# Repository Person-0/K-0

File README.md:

# **K-0**

75% Keyboard with thocky switches. USB-C / BLE connectivity, fully custom 3d printed case + PCB.

## The Idea

Always wanted to design a keyboard for myself. Decided to finally go for it.

After searching online about various keyboards and switches, I realized I love deep thocky-sounding keyboards, so I selected the `Akko Bittersweet` switches. They are tactile switches with an operating force of 48 ± 5gf and tactile force of 60 ± 5gf. ([more switch specs](https://en.akkogear.com/product/bittersweet-switch-lubed/), [sound test](https://www.youtube.com/watch?v=nj9W8xXELII)).

The layout of the keyboard will be 60%, with no separate arrow keys or navigation cluster BUT with an added function keys row.

The microcontroller I have selected for this project is the `MDBT50Q-P1M nRF52840 Based BLE Module` for it's built-in bluetooth capabilities and good support ecosystem for similar projects. This will be paired up with a 1s (3.7V) LiPo battery with a suitable capacity + custom charging circuit which will be good enough for our usecase.

### Keyboard layout (from [keyboard-layout-editor.com](https://keyboard-layout-editor.com)):

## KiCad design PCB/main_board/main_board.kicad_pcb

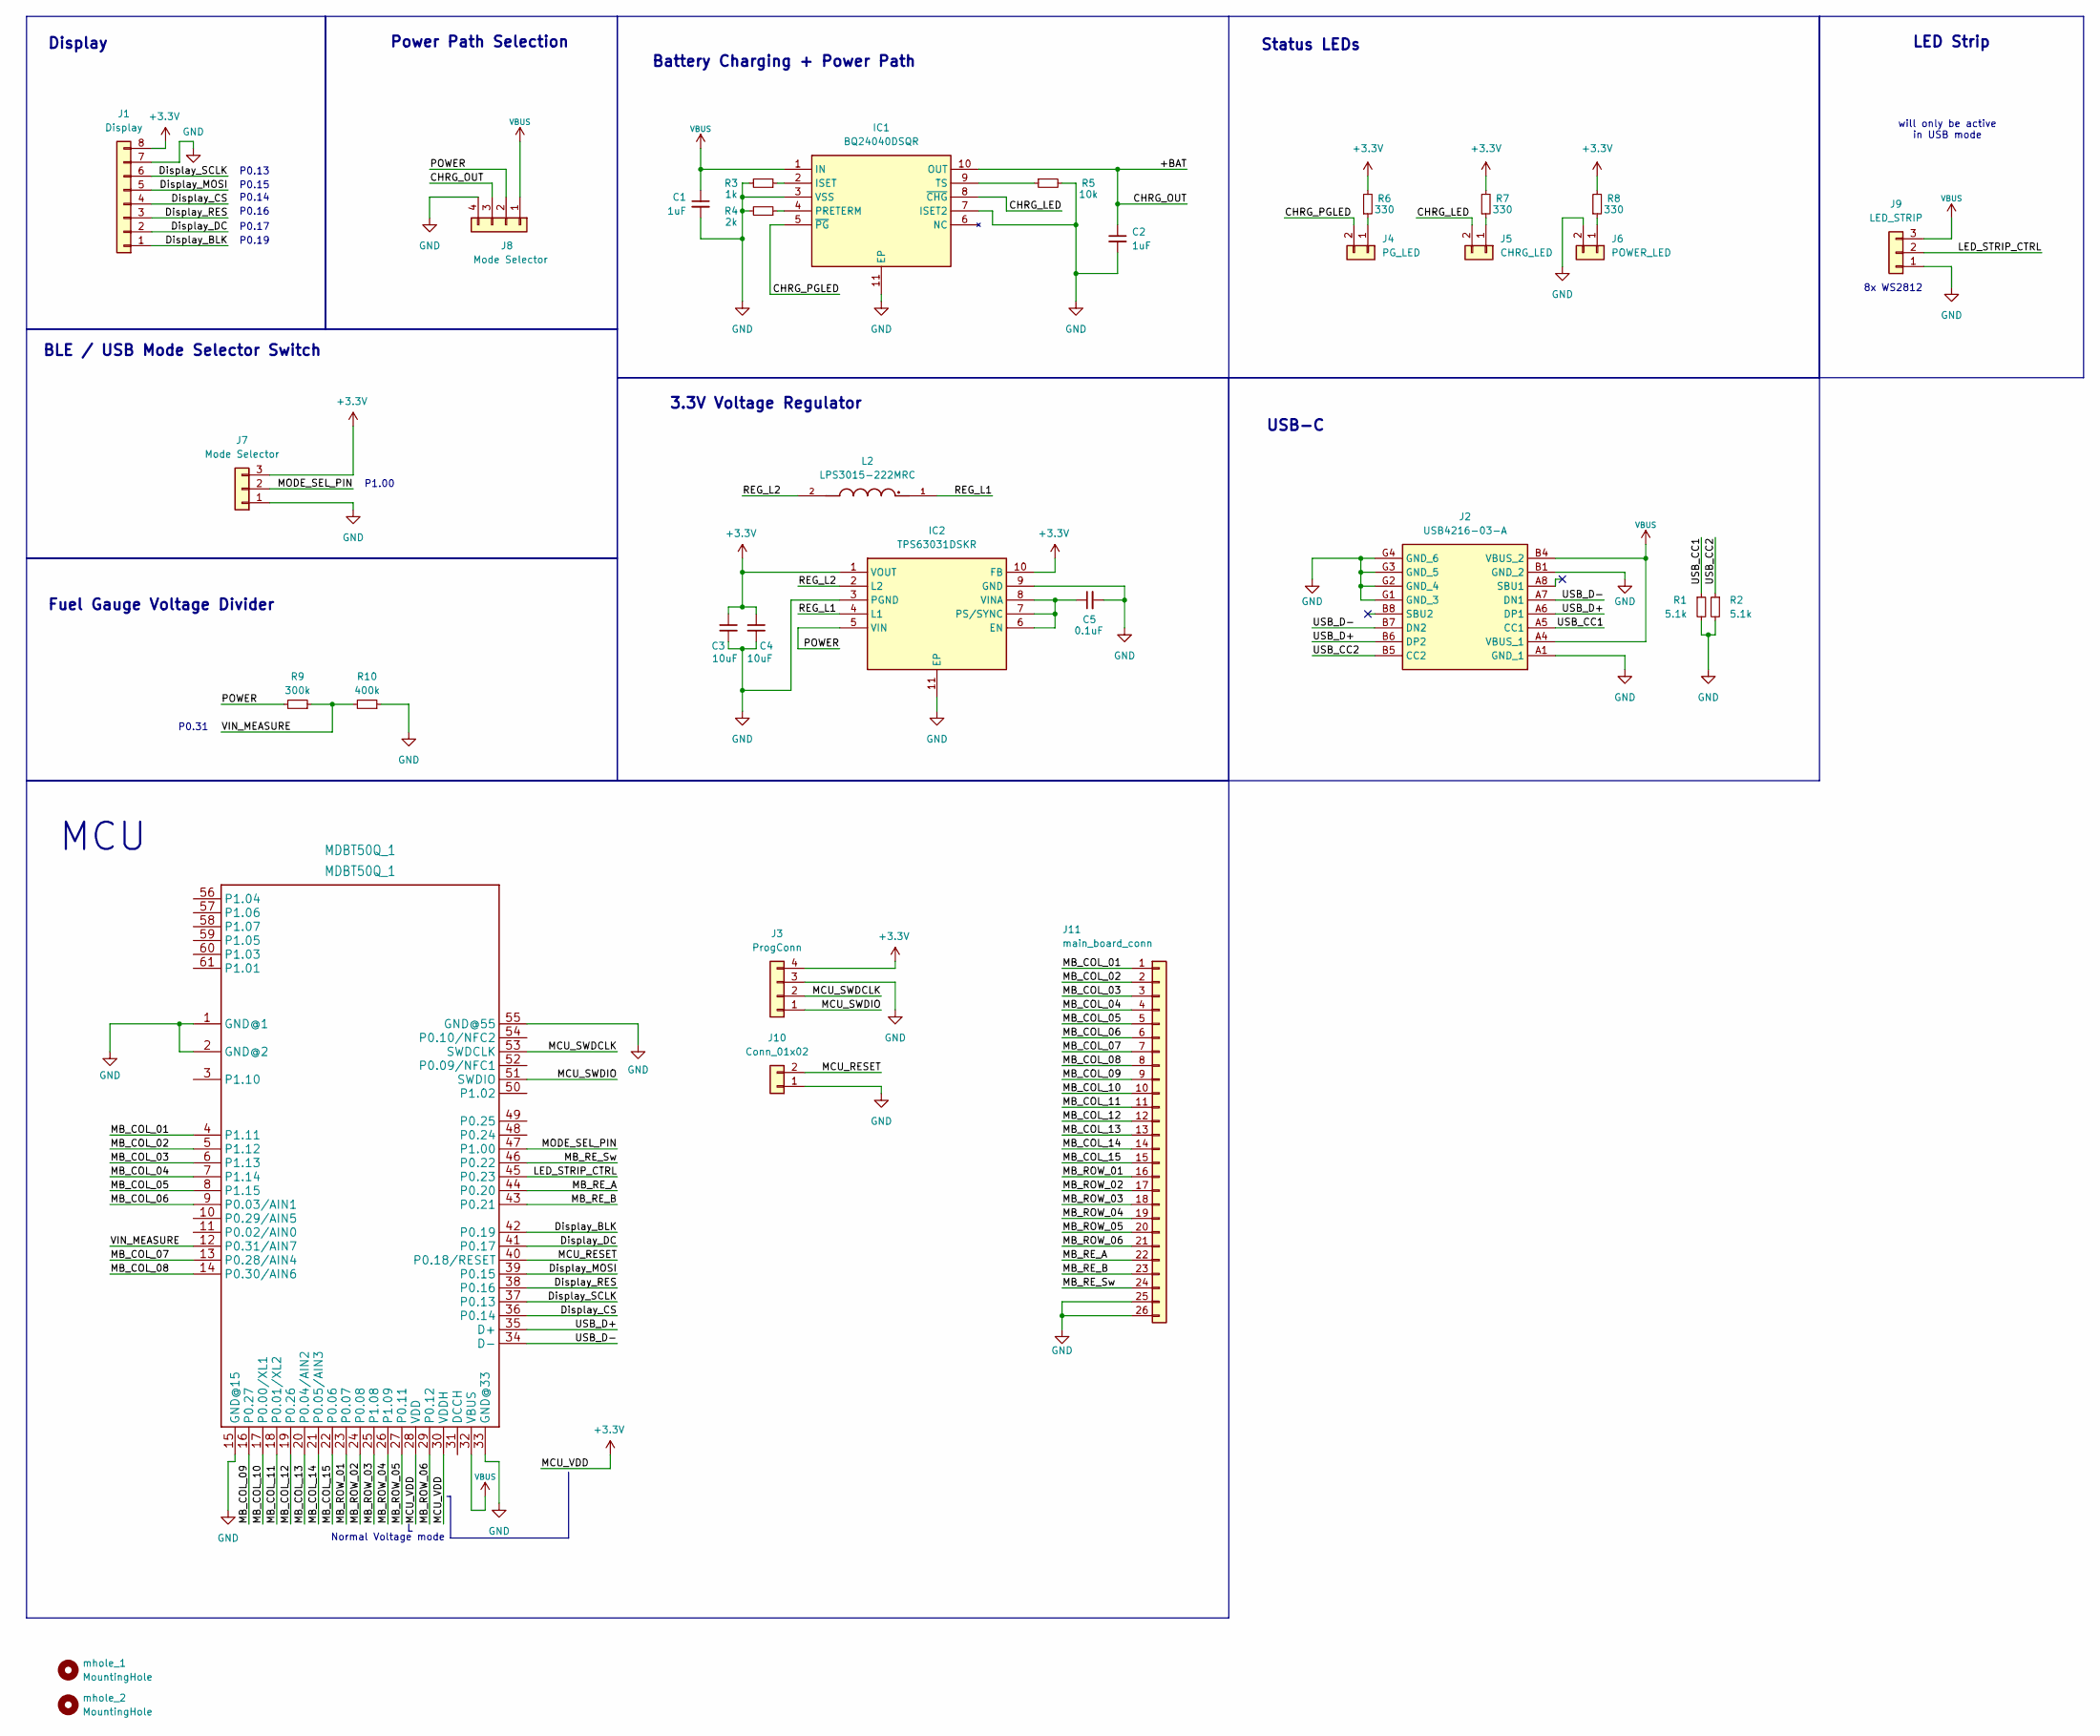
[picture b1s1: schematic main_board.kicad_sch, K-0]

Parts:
C1, C2: 1uF; C_0402_1005Metric; Manufacturer_Part_Number CC0402KRX5R6BB105
C3, C4: 10uF; C_0402_1005Metric; Manufacturer_Part_Number CC0402MRX5R5BB106
C5: 0.1uF; C_0402_1005Metric; Manufacturer_Part_Number MC0402B104K160CT
IC1: BQ24040DSQR; SON40P200X200X80-11N; Mouser Part Number 595-BQ24040DSQR
IC2: TPS63031DSKR; SON50P250X250X80-11N-D; Mouser Part Number 595-TPS63031DSKR
J1: Display; PinHeader_1x08_P2.54mm_Vertical
J2: USB4216-03-A; USB421603A; Mouser Part Number 640-USB4216-03-A
J3: ProgConn; PinHeader_1x04_P2.54mm_Vertical
J4: PG_LED; PinHeader_1x02_P2.54mm_Vertical
J5: CHRG_LED; PinHeader_1x02_P2.54mm_Vertical
J6: POWER_LED; PinHeader_1x02_P2.54mm_Vertical
J7: Mode Selector; PinHeader_1x03_P2.54mm_Vertical
J8: Mode Selector; PinHeader_1x04_P2.54mm_Vertical
J9: LED_STRIP; PinHeader_1x03_P2.54mm_Vertical
J10: Conn_01x02; PinHeader_1x02_P2.54mm_Vertical
J11: main_board_conn; PinHeader_1x26_P2.54mm_Vertical
L2: LPS3015-222MRC; IND_LPS3015-222MRC; PARTREV 12/13/21
MDBT50Q_1: MDBT50Q_1; Raytac_MDBT50Q; Manufacturer_Part_Number 113990583
R1, R2: 5.1k; R_0402_1005Metric; Manufacturer_Part_Number CR0402-JW-512GLF
R3: 1k; PinHeader_1x02_P2.54mm_Vertical
R4: 2k; PinHeader_1x02_P2.54mm_Vertical
R5: 10k; PinHeader_1x02_P2.54mm_Vertical
R6, R7, R8: 330; PinHeader_1x02_P2.54mm_Vertical
R9: 300k; PinHeader_1x02_P2.54mm_Vertical
R10: 400k; PinHeader_1x02_P2.54mm_Vertical
mhole_1, mhole_2: MountingHole; MountingHole_3mm

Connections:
+3.3V: C3.1, C4.1, IC2.1 (VOUT), IC2.10 (FB), J1.8, J3.4, J7.3, MDBT50Q_1.28 (VDD), MDBT50Q_1.30 (VDDH), R6.2, R7.2, R8.2
/+BAT: C2.1, IC1.10 (OUT), J8.3
/CHRG_LED: IC1.8 (~CHG), J5.2
/CHRG_PGLED: IC1.5 (~PG), J4.2
/Display_BLK: J1.1, MDBT50Q_1.42 (P0.19)
/Display_CS: J1.4, MDBT50Q_1.36 (P0.14)
/Display_DC: J1.2, MDBT50Q_1.41 (P0.17)
/Display_MOSI: J1.5, MDBT50Q_1.39 (P0.15)
/Display_RES: J1.3, MDBT50Q_1.38 (P0.16)
/Display_SCLK: J1.6, MDBT50Q_1.37 (P0.13)
/LED_STRIP_CTRL: J9.2, MDBT50Q_1.45 (P0.23)
/MB_COL_01: J11.1, MDBT50Q_1.4 (P1.11)
/MB_COL_02: J11.2, MDBT50Q_1.5 (P1.12)
/MB_COL_03: J11.3, MDBT50Q_1.6 (P1.13)
/MB_COL_04: J11.4, MDBT50Q_1.7 (P1.14)
/MB_COL_05: J11.5, MDBT50Q_1.8 (P1.15)
/MB_COL_06: J11.6, MDBT50Q_1.9 (P0.03/AIN1)
/MB_COL_07: J11.7, MDBT50Q_1.13 (P0.28/AIN4)
/MB_COL_08: J11.8, MDBT50Q_1.14 (P0.30/AIN6)
/MB_COL_09: J11.9, MDBT50Q_1.16 (P0.27)
/MB_COL_10: J11.10, MDBT50Q_1.17 (P0.00/XL1)
/MB_COL_11: J11.11, MDBT50Q_1.18 (P0.01/XL2)
/MB_COL_12: J11.12, MDBT50Q_1.19 (P0.26)
/MB_COL_13: J11.13, MDBT50Q_1.20 (P0.04/AIN2)
/MB_COL_14: J11.14, MDBT50Q_1.21 (P0.05/AIN3)
/MB_COL_15: J11.15, MDBT50Q_1.22 (P0.06)
/MB_RE_A: J11.22, MDBT50Q_1.44 (P0.20)
/MB_RE_B: J11.23, MDBT50Q_1.43 (P0.21)
/MB_RE_Sw: J11.24, MDBT50Q_1.46 (P0.22)
/MB_ROW_01: J11.16, MDBT50Q_1.23 (P0.07)
/MB_ROW_02: J11.17, MDBT50Q_1.24 (P0.08)
/MB_ROW_03: J11.18, MDBT50Q_1.25 (P1.08)
/MB_ROW_04: J11.19, MDBT50Q_1.26 (P1.09)
/MB_ROW_05: J11.20, MDBT50Q_1.27 (P0.11)
/MB_ROW_06: J11.21, MDBT50Q_1.29 (P0.12)
/MCU_RESET: J10.2, MDBT50Q_1.40 (P0.18/RESET)
/MCU_SWDCLK: J3.2, MDBT50Q_1.53 (SWDCLK)
/MCU_SWDIO: J3.1, MDBT50Q_1.51 (SWDIO)
/MODE_SEL_PIN: J7.2, MDBT50Q_1.47 (P1.00)
/POWER: IC2.5 (VIN), J8.2, R9.2
/REG_L1: IC2.4 (L1), L2.1
/REG_L2: IC2.2 (L2), L2.2
/USB_CC1: J2.A5 (CC1), R1.1
/USB_CC2: J2.B5 (CC2), R2.1
/USB_D+: J2.A6 (DP1), J2.B6 (DP2), MDBT50Q_1.35 (D+)
/USB_D-: J2.A7 (DN1), J2.B7 (DN2), MDBT50Q_1.34 (D-)
/VIN_MEASURE: MDBT50Q_1.12 (P0.31/AIN7), R9.1, R10.2
GND: C1.2, C2.2, C3.2, C4.2, C5.2, IC1.3 (VSS), IC1.7 (ISET2), IC1.11 (EP), IC2.3 (PGND), IC2.9 (GND), IC2.11 (EP), J1.7, J2.A1 (GND_1), J2.B1 (GND_2), J2.G1 (GND_3), J2.G2 (GND_4), J2.G3 (GND_5), J2.G4 (GND_6), J3.3, J6.2, J7.1, J8.4, J9.1, J10.1, J11.25, J11.26, MDBT50Q_1.1 (GND@1), MDBT50Q_1.2 (GND@2), MDBT50Q_1.15 (GND@15), MDBT50Q_1.33 (GND@33), MDBT50Q_1.55 (GND@55), R1.2, R2.2, R3.2, R4.2, R5.2, R10.1
unnamed: IC1.2 (ISET), R3.1
unnamed: IC1.4 (PRETERM), R4.1
unnamed: IC1.9 (TS), R5.1
unnamed: C5.1, IC2.6 (EN), IC2.7 (PS/SYNC), IC2.8 (VINA)
unnamed: J4.1, R6.1
unnamed: J5.1, R7.1
unnamed: J6.1, R8.1
VBUS: C1.1, IC1.1 (IN), J2.A4 (VBUS_1), J2.B4 (VBUS_2), J8.1, J9.3, MDBT50Q_1.32 (VBUS)

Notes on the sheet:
P0.16
USB-C
P0.14
BLE / USB Mode Selector Switch
Status LEDs
Normal Voltage mode
LED Strip
P0.19
3.3V Voltage Regulator
P0.17
will only be active in USB mode
Battery Charging + Power Path
8x WS2812
Display
P0.13
P0.15
P0.31
MCU
P1.00
Power Path Selection
Fuel Gauge Voltage Divider

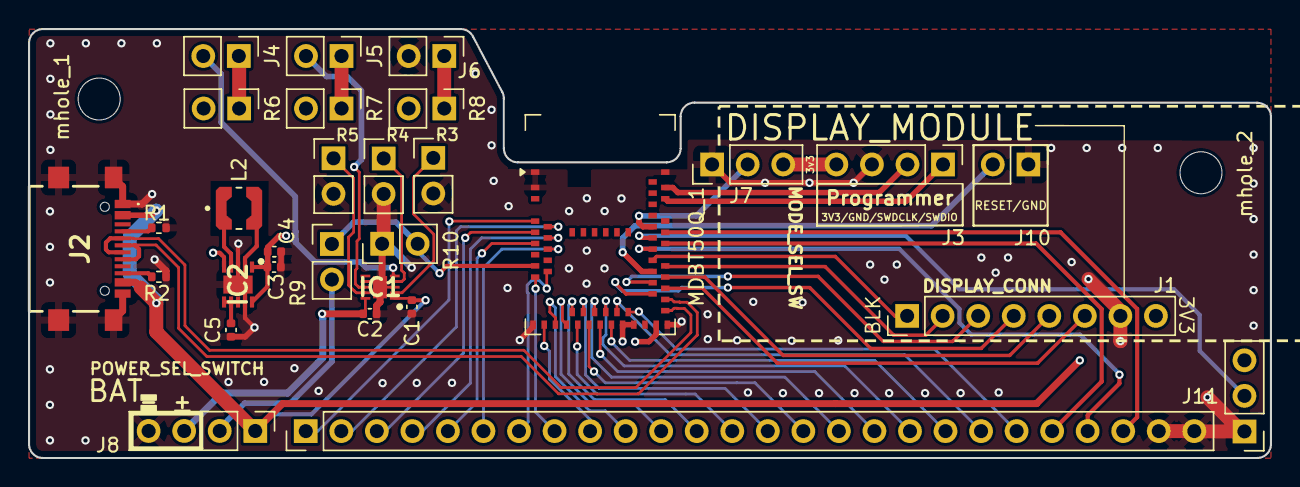
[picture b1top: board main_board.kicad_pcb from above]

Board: 4 copper layers, 88.8 x 30.7 mm, 32 parts (0 on the bottom side), 56 nets.

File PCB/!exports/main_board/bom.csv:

"Reference","Qty","Value","DNP","Exclude from BOM","Footprint","Datasheet","Manufacturer_Part_Number"
"C1,C2","2","1uF","","","Capacitor_SMD:C_0402_1005Metric","https://prod-parts-data.s3.amazonaws.com/CC0402KRX5R6BB105/d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","CC0402KRX5R6BB105"
"C3,C4","2","10uF","","","Capacitor_SMD:C_0402_1005Metric","https://prod-parts-data.s3.amazonaws.com/CC0402MRX5R5BB106/d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","CC0402MRX5R5BB106"
"C5","1","0.1uF","","","Capacitor_SMD:C_0402_1005Metric","https://prod-parts-data.s3.amazonaws.com/MC0402B104K160CT/da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","MC0402B104K160CT"
"IC1","1","BQ24040DSQR","","","BQ24040DSQR-lion:SON40P200X200X80-11N","http://www.ti.com/lit/gpn/bq24040","BQ24040DSQR"
"IC2","1","TPS63031DSKR","","","TPS63031DSKR-lion:SON50P250X250X80-11N-D","http://www.ti.com/general/docs/suppproductinfo.tsp?distId=10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","TPS63031DSKR"
"J2","1","USB4216-03-A","","","USB421603A","","USB4216-03-A"
"J10","1","Conn_01x02","","","Connector_PinHeader_2.54mm:PinHeader_1x02_P2.54mm_Vertical","~",""
"J11","1","main_board_conn","","","Connector_PinHeader_2.54mm:PinHeader_1x26_P2.54mm_Vertical","~",""
"L2","1","LPS3015-222MRC","","","LPS3015-222MRC:IND_LPS3015-222MRC","https://prod-parts-data.s3.amazonaws.com/LPS3015-222MRC/data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","LPS3015-222MRC"
"MDBT50Q_1","1","MDBT50Q_1","","","RF_Module:Raytac_MDBT50Q","https://www.mouser.in/datasheet/3/1361/1/nRF52840_MDBT50Q_1M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","113990583"
"R1,R2","2","5.1k","","","Resistor_SMD:R_0402_1005Metric","https://prod-parts-data.s3.amazonaws.com/CR0402-JW-512GLF/da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","CR0402-JW-512GLF"

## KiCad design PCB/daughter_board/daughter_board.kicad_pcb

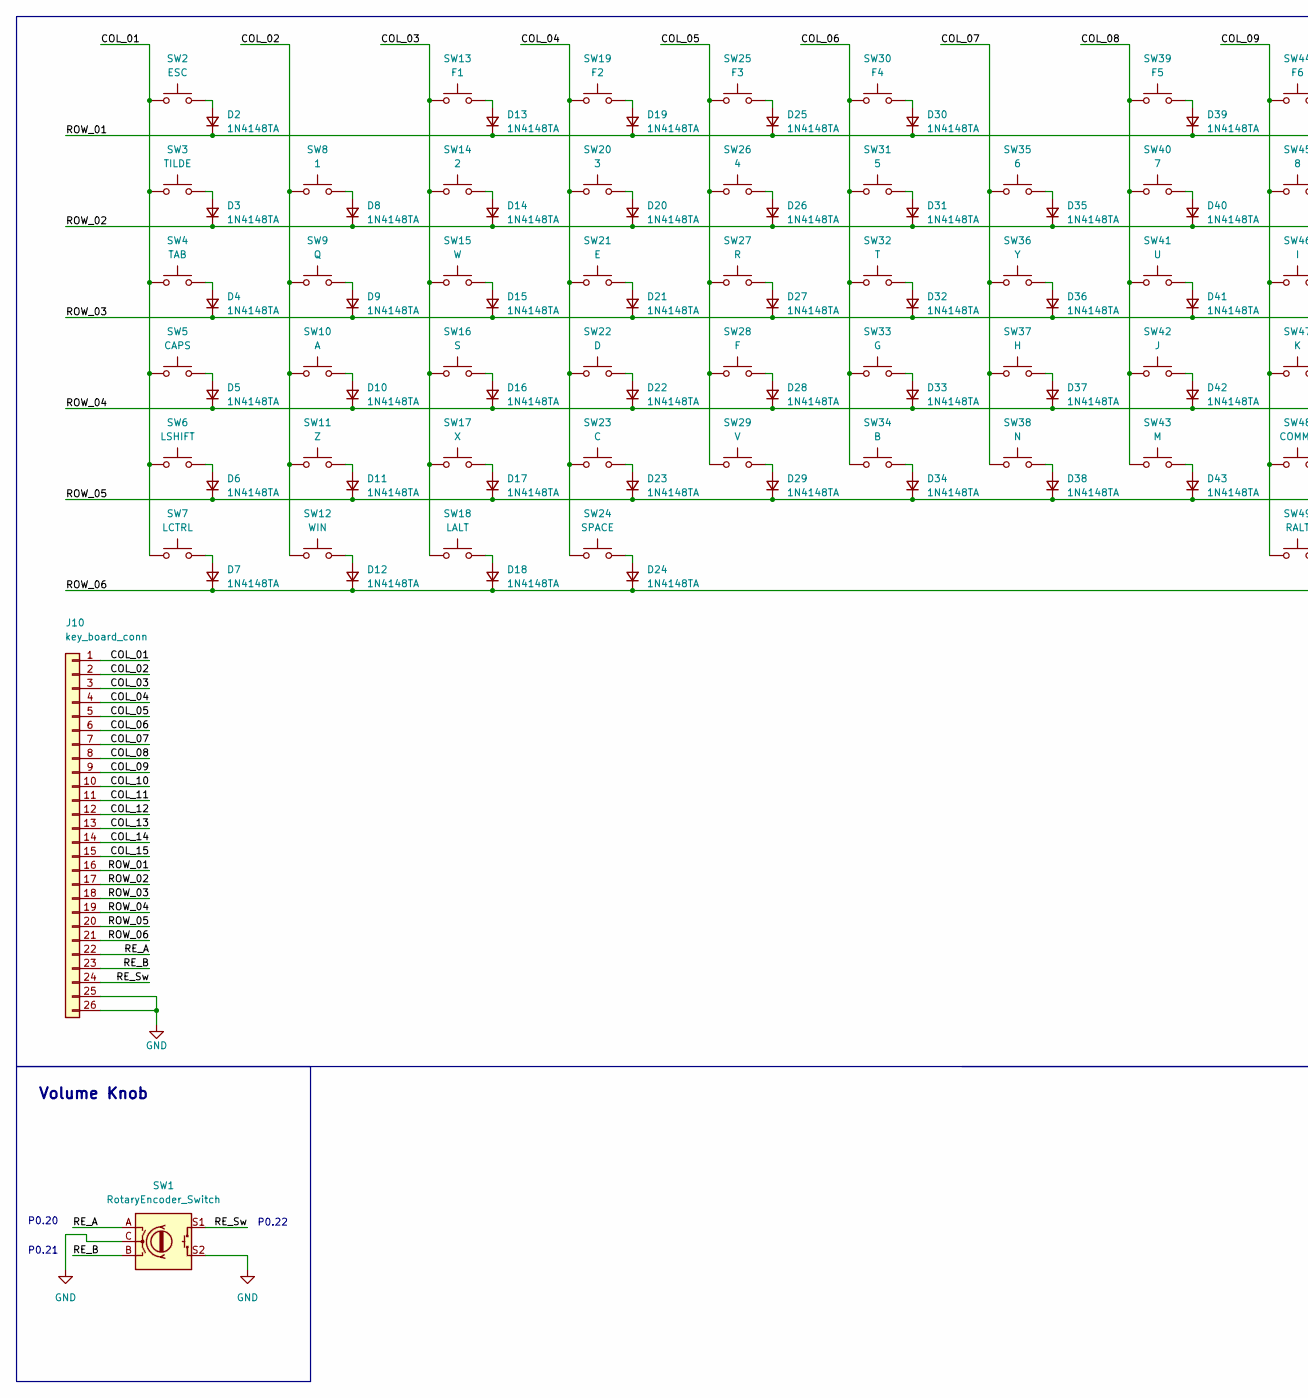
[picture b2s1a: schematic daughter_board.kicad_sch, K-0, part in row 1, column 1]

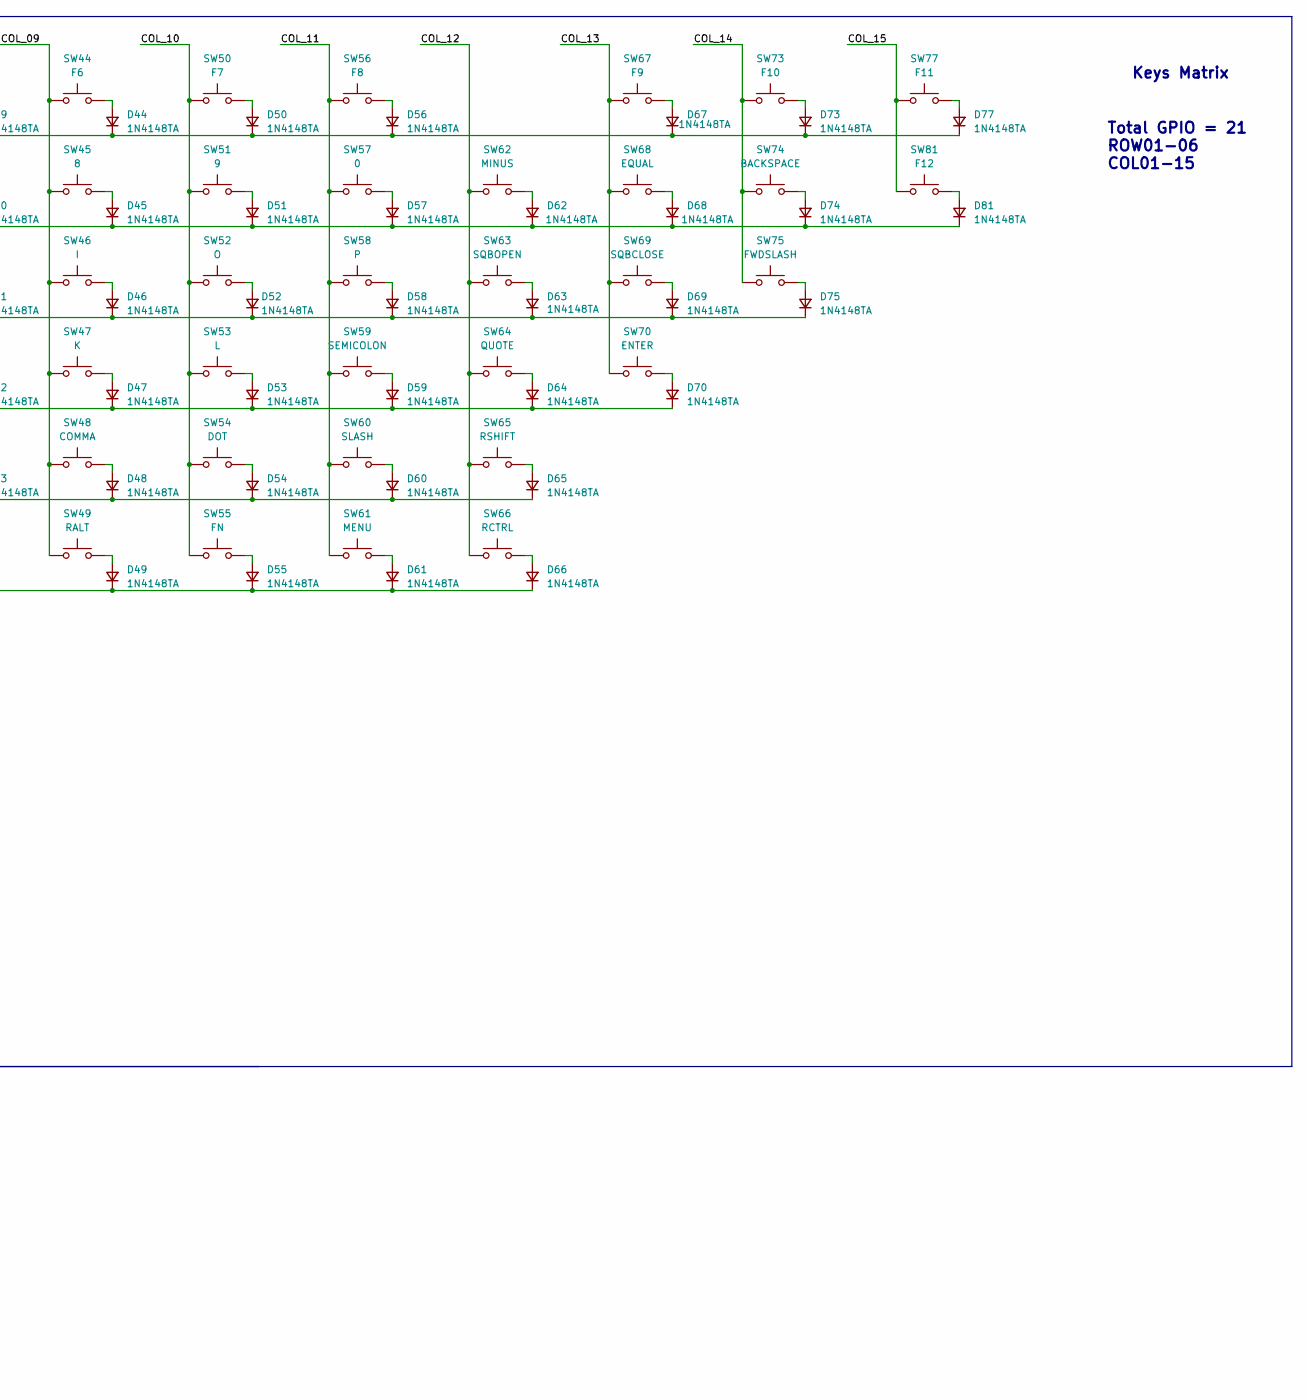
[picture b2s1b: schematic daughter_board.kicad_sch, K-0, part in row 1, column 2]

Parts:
D2, D3, D4, D5, D6, D7, D8, D9, D10, D11, D12, D13, D14, D15, D16, D17, D18, D19, D20, D21, D22, D23, D24, D25, D26, D27, D28, D29, D30, D31, D32, D33, D34, D35, D36, D37, D38, D39, D40, D41, D42, D43, D44, D45, D46, D47, D48, D49, D50, D51, D52, D53, D54, D55, D56, D57, D58, D59, D60, D61, D62, D63, D64, D65, D66, D67, D68, D69, D70, D73, D74, D75, D77, D81: 1N4148TA; D_DO-35_SOD27_P7.62mm_Horizontal; Manufacturer_Part_Number 1N4148WS
J10: key_board_conn; PinHeader_1x26_P2.54mm_Vertical
SW1: RotaryEncoder_Switch; RotaryEncoder_Alps_EC11E-Switch_Vertical_H20mm
SW2: ESC; 3Dfyd_SW_Cherry_MX_1.00u_PCB
SW3: TILDE; 3Dfyd_SW_Cherry_MX_1.00u_PCB
SW4: TAB; 3Dfyd_SW_Cherry_MX_1.50u_PCB
SW5: CAPS; 3Dfyd_SW_Cherry_MX_1.75u_PCB
SW6: LSHIFT; 3Dfyd_SW_Cherry_MX_2.25u_PCB
SW7: LCTRL; 3dfyd_SW_Cherry_MX_1.25u_PCB
SW8: 1; 3Dfyd_SW_Cherry_MX_1.00u_PCB
SW9: Q; 3Dfyd_SW_Cherry_MX_1.00u_PCB
SW10: A; 3Dfyd_SW_Cherry_MX_1.00u_PCB
SW11: Z; 3Dfyd_SW_Cherry_MX_1.00u_PCB
SW12: WIN; 3dfyd_SW_Cherry_MX_1.25u_PCB
SW13: F1; 3Dfyd_SW_Cherry_MX_1.00u_PCB
SW14: 2; 3Dfyd_SW_Cherry_MX_1.00u_PCB
SW15: W; 3Dfyd_SW_Cherry_MX_1.00u_PCB
SW16: S; 3Dfyd_SW_Cherry_MX_1.00u_PCB
SW17: X; 3Dfyd_SW_Cherry_MX_1.00u_PCB
SW18: LALT; 3dfyd_SW_Cherry_MX_1.25u_PCB
SW19: F2; 3Dfyd_SW_Cherry_MX_1.00u_PCB
SW20: 3; 3Dfyd_SW_Cherry_MX_1.00u_PCB
SW21: E; 3Dfyd_SW_Cherry_MX_1.00u_PCB
SW22: D; 3Dfyd_SW_Cherry_MX_1.00u_PCB
SW23: C; 3Dfyd_SW_Cherry_MX_1.00u_PCB
SW24: SPACE; 3Dfyd_SW_Cherry_MX_6.25u_PCB
SW25: F3; 3Dfyd_SW_Cherry_MX_1.00u_PCB
SW26: 4; 3Dfyd_SW_Cherry_MX_1.00u_PCB
SW27: R; 3Dfyd_SW_Cherry_MX_1.00u_PCB
SW28: F; 3Dfyd_SW_Cherry_MX_1.00u_PCB
SW29: V; 3Dfyd_SW_Cherry_MX_1.00u_PCB
SW30: F4; 3Dfyd_SW_Cherry_MX_1.00u_PCB
SW31: 5; 3Dfyd_SW_Cherry_MX_1.00u_PCB
SW32: T; 3Dfyd_SW_Cherry_MX_1.00u_PCB
SW33: G; 3Dfyd_SW_Cherry_MX_1.00u_PCB
SW34: B; 3Dfyd_SW_Cherry_MX_1.00u_PCB
SW35: 6; 3Dfyd_SW_Cherry_MX_1.00u_PCB
SW36: Y; 3Dfyd_SW_Cherry_MX_1.00u_PCB
SW37: H; 3Dfyd_SW_Cherry_MX_1.00u_PCB
SW38: N; 3Dfyd_SW_Cherry_MX_1.00u_PCB
SW39: F5; 3Dfyd_SW_Cherry_MX_1.00u_PCB
SW40: 7; 3Dfyd_SW_Cherry_MX_1.00u_PCB
SW41: U; 3Dfyd_SW_Cherry_MX_1.00u_PCB
SW42: J; 3Dfyd_SW_Cherry_MX_1.00u_PCB
SW43: M; 3Dfyd_SW_Cherry_MX_1.00u_PCB
SW44: F6; 3Dfyd_SW_Cherry_MX_1.00u_PCB
SW45: 8; 3Dfyd_SW_Cherry_MX_1.00u_PCB
SW46: I; 3Dfyd_SW_Cherry_MX_1.00u_PCB
SW47: K; 3Dfyd_SW_Cherry_MX_1.00u_PCB
SW48: COMMA; 3Dfyd_SW_Cherry_MX_1.00u_PCB
SW49: RALT; 3dfyd_SW_Cherry_MX_1.25u_PCB
SW50: F7; 3Dfyd_SW_Cherry_MX_1.00u_PCB
SW51: 9; 3Dfyd_SW_Cherry_MX_1.00u_PCB
SW52: O; 3Dfyd_SW_Cherry_MX_1.00u_PCB
SW53: L; 3Dfyd_SW_Cherry_MX_1.00u_PCB
SW54: DOT; 3Dfyd_SW_Cherry_MX_1.00u_PCB
SW55: FN; 3dfyd_SW_Cherry_MX_1.25u_PCB
SW56: F8; 3Dfyd_SW_Cherry_MX_1.00u_PCB
SW57: 0; 3Dfyd_SW_Cherry_MX_1.00u_PCB
SW58: P; 3Dfyd_SW_Cherry_MX_1.00u_PCB
SW59: SEMICOLON; 3Dfyd_SW_Cherry_MX_1.00u_PCB
SW60: SLASH; 3Dfyd_SW_Cherry_MX_1.00u_PCB
SW61: MENU; 3dfyd_SW_Cherry_MX_1.25u_PCB
SW62: MINUS; 3Dfyd_SW_Cherry_MX_1.00u_PCB
SW63: SQBOPEN; 3Dfyd_SW_Cherry_MX_1.00u_PCB
SW64: QUOTE; 3Dfyd_SW_Cherry_MX_1.00u_PCB
SW65: RSHIFT; 3Dfyd_SW_Cherry_MX_2.75u_PCB
SW66: RCTRL; 3dfyd_SW_Cherry_MX_1.25u_PCB
SW67: F9; 3Dfyd_SW_Cherry_MX_1.00u_PCB
SW68: EQUAL; 3Dfyd_SW_Cherry_MX_1.00u_PCB
SW69: SQBCLOSE; 3Dfyd_SW_Cherry_MX_1.00u_PCB
SW70: ENTER; 3Dfyd_SW_Cherry_MX_2.25u_PCB
SW73: F10; 3Dfyd_SW_Cherry_MX_1.00u_PCB
SW74: BACKSPACE; 3Dfyd_SW_Cherry_MX_2.00u_PCB
SW75: FWDSLASH; 3Dfyd_SW_Cherry_MX_1.50u_PCB
SW77: F11; 3Dfyd_SW_Cherry_MX_1.00u_PCB
SW81: F12; 3Dfyd_SW_Cherry_MX_1.00u_PCB

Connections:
/COL_01: J10.1, SW2.1, SW3.1, SW4.1, SW5.1, SW6.1, SW7.1
/COL_02: J10.2, SW8.1, SW9.1, SW10.1, SW11.1, SW12.1
/COL_03: J10.3, SW13.1, SW14.1, SW15.1, SW16.1, SW17.1, SW18.1
/COL_04: J10.4, SW19.1, SW20.1, SW21.1, SW22.1, SW23.1, SW24.1
/COL_05: J10.5, SW25.1, SW26.1, SW27.1, SW28.1, SW29.1
/COL_06: J10.6, SW30.1, SW31.1, SW32.1, SW33.1, SW34.1
/COL_07: J10.7, SW35.1, SW36.1, SW37.1, SW38.1
/COL_08: J10.8, SW39.1, SW40.1, SW41.1, SW42.1, SW43.1
/COL_09: J10.9, SW44.1, SW45.1, SW46.1, SW47.1, SW48.1, SW49.1
/COL_10: J10.10, SW50.1, SW51.1, SW52.1, SW53.1, SW54.1, SW55.1
/COL_11: J10.11, SW56.1, SW57.1, SW58.1, SW59.1, SW60.1, SW61.1
/COL_12: J10.12, SW62.1, SW63.1, SW64.1, SW65.1, SW66.1
/COL_13: J10.13, SW67.1, SW68.1, SW69.1, SW70.1
/COL_14: J10.14, SW73.1, SW74.1, SW75.1
/COL_15: J10.15, SW77.1, SW81.1
/RE_A: J10.22, SW1.A
/RE_B: J10.23, SW1.B
/RE_Sw: J10.24, SW1.S1
/ROW_01: D2.1 (K), D13.1 (K), D19.1 (K), D25.1 (K), D30.1 (K), D39.1 (K), D44.1 (K), D50.1 (K), D56.1 (K), D67.1 (K), D73.1 (K), D77.1 (K), J10.16
/ROW_02: D3.1 (K), D8.1 (K), D14.1 (K), D20.1 (K), D26.1 (K), D31.1 (K), D35.1 (K), D40.1 (K), D45.1 (K), D51.1 (K), D57.1 (K), D62.1 (K), D68.1 (K), D74.1 (K), D81.1 (K), J10.17
/ROW_03: D4.1 (K), D9.1 (K), D15.1 (K), D21.1 (K), D27.1 (K), D32.1 (K), D36.1 (K), D41.1 (K), D46.1 (K), D52.1 (K), D58.1 (K), D63.1 (K), D69.1 (K), D75.1 (K), J10.18
/ROW_04: D5.1 (K), D10.1 (K), D16.1 (K), D22.1 (K), D28.1 (K), D33.1 (K), D37.1 (K), D42.1 (K), D47.1 (K), D53.1 (K), D59.1 (K), D64.1 (K), D70.1 (K), J10.19
/ROW_05: D6.1 (K), D11.1 (K), D17.1 (K), D23.1 (K), D29.1 (K), D34.1 (K), D38.1 (K), D43.1 (K), D48.1 (K), D54.1 (K), D60.1 (K), D65.1 (K), J10.20
/ROW_06: D7.1 (K), D12.1 (K), D18.1 (K), D24.1 (K), D49.1 (K), D55.1 (K), D61.1 (K), D66.1 (K), J10.21
GND: J10.25, J10.26, SW1.C, SW1.S2
unnamed: D2.2 (A), SW2.2
unnamed: D3.2 (A), SW3.2
unnamed: D4.2 (A), SW4.2
unnamed: D5.2 (A), SW5.2
unnamed: D6.2 (A), SW6.2
unnamed: D7.2 (A), SW7.2
unnamed: D8.2 (A), SW8.2
unnamed: D9.2 (A), SW9.2
unnamed: D10.2 (A), SW10.2
unnamed: D11.2 (A), SW11.2
unnamed: D12.2 (A), SW12.2
unnamed: D13.2 (A), SW13.2
unnamed: D14.2 (A), SW14.2
unnamed: D15.2 (A), SW15.2
unnamed: D16.2 (A), SW16.2
unnamed: D17.2 (A), SW17.2
unnamed: D18.2 (A), SW18.2
unnamed: D19.2 (A), SW19.2
unnamed: D20.2 (A), SW20.2
unnamed: D21.2 (A), SW21.2
unnamed: D22.2 (A), SW22.2
unnamed: D23.2 (A), SW23.2
unnamed: D24.2 (A), SW24.2
unnamed: D25.2 (A), SW25.2
unnamed: D26.2 (A), SW26.2
unnamed: D27.2 (A), SW27.2
unnamed: D28.2 (A), SW28.2
unnamed: D29.2 (A), SW29.2
unnamed: D30.2 (A), SW30.2
unnamed: D31.2 (A), SW31.2
unnamed: D32.2 (A), SW32.2
unnamed: D33.2 (A), SW33.2
unnamed: D34.2 (A), SW34.2
unnamed: D35.2 (A), SW35.2
unnamed: D36.2 (A), SW36.2
unnamed: D37.2 (A), SW37.2
unnamed: D38.2 (A), SW38.2
unnamed: D39.2 (A), SW39.2
unnamed: D40.2 (A), SW40.2
unnamed: D41.2 (A), SW41.2
unnamed: D42.2 (A), SW42.2
unnamed: D43.2 (A), SW43.2
unnamed: D44.2 (A), SW44.2
unnamed: D45.2 (A), SW45.2
unnamed: D46.2 (A), SW46.2
unnamed: D47.2 (A), SW47.2
unnamed: D48.2 (A), SW48.2
unnamed: D49.2 (A), SW49.2
unnamed: D50.2 (A), SW50.2
unnamed: D51.2 (A), SW51.2
unnamed: D52.2 (A), SW52.2
unnamed: D53.2 (A), SW53.2
unnamed: D54.2 (A), SW54.2
unnamed: D55.2 (A), SW55.2
unnamed: D56.2 (A), SW56.2
unnamed: D57.2 (A), SW57.2
unnamed: D58.2 (A), SW58.2
unnamed: D59.2 (A), SW59.2
unnamed: D60.2 (A), SW60.2
unnamed: D61.2 (A), SW61.2
unnamed: D62.2 (A), SW62.2
unnamed: D63.2 (A), SW63.2
unnamed: D64.2 (A), SW64.2
unnamed: D65.2 (A), SW65.2
unnamed: D66.2 (A), SW66.2
unnamed: D67.2 (A), SW67.2
unnamed: D68.2 (A), SW68.2
unnamed: D69.2 (A), SW69.2
unnamed: D70.2 (A), SW70.2
unnamed: D73.2 (A), SW73.2
unnamed: D74.2 (A), SW74.2
unnamed: D75.2 (A), SW75.2
unnamed: D77.2 (A), SW77.2
unnamed: D81.2 (A), SW81.2

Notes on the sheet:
P0.20
P0.22
Volume Knob
P0.21
Keys Matrix
Total GPIO = 21 ROW01-06 COL01-15

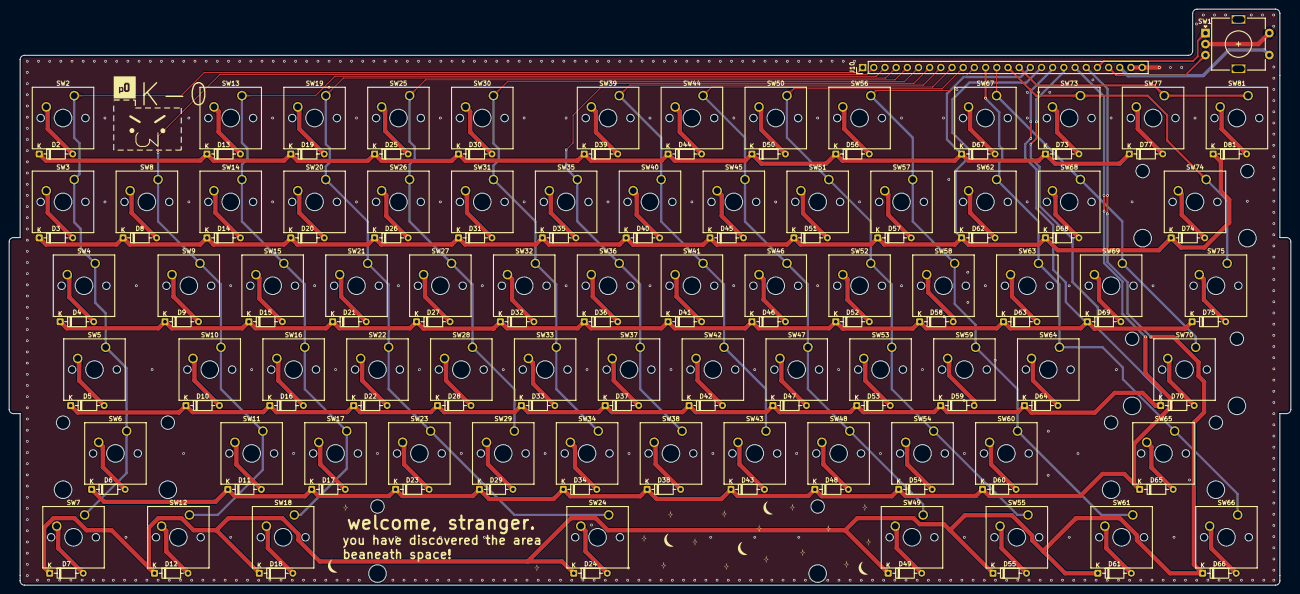
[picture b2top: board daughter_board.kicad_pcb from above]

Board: 2 copper layers, 291.2 x 130.9 mm, 150 parts (0 on the bottom side), 99 nets.
